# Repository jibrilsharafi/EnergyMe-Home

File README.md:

#  EnergyMe-Home

<div align="center">

<h3>🛒 Want it ready to use? Pre-assembled and calibrated units. Just install and monitor!</h3>

Available on our <a href="https://www.energyme.net/shop">website</a> and on <a href="https://www.tindie.com/stores/energyme/">Tindie</a>

</div>

*EnergyMe-Home* is an open-source energy monitoring system for home use, capable of monitoring up to 16 circuits. It integrates with any platform through REST API, MQTT, Modbus TCP, and InfluxDB.

Built for makers and DIY enthusiasts who want to track their home's energy consumption. The hardware uses ESP32-S3 and ADE7953 energy measurement IC, while the firmware is written in C++ with PlatformIO and Arduino framework. You can build and customize it yourself - all hardware designs and software are open-source. Prefer it ready to go? Grab a [pre-assembled unit](https://www.energyme.net/shop).

> A demo speaks more than 1000 words: try the [demo dashboard](https://demo-energyme-home.energyme.net)!

> **Join the community!** Head over to [GitHub Discussions](https://github.com/jibrilsharafi/EnergyMe-Home/discussions) - ask questions, share your builds and dashboards, suggest features, and exchange integration tips. It's the home for everyone building, installing, or tinkering with EnergyMe-Home

## Supported Electrical Systems

EnergyMe-Home is compatible with various electrical systems worldwide:

| System Type | Voltage | Configuration | Supported |
|-------------|---------|---------------|-----------|
| **Single Phase** | 230V | L + N | ✅ Europe, Asia, Africa, Oceania |
| **Split Phase** | 120V/240V | L1 + L2 + N | ✅ North America residential |
| **Split Phase** | 120V/240V | L1 + L2 (no N) | ✅ Old electrical systems |
| **Three Phase** | 400V/230V | 3L + N | ❕ Europe commercial/industrial (derived voltages) |
| **Three Phase** | 208V/120V | 3L + N | ❕ North America commercial (derived voltages) |

**Current Transformers Supported:**

- 333 mV output CTs (+- 500 mV absolute)
- 3.5 mm jack connectors for easy plug-and-play

**Monitoring Capacity:**

- Up to **16 circuits** simultaneously
- 1× main circuit, sampled at high frequency for accurate total energy measurement
- 15× branch circuits, multiplexed for individual monitoring

⚠️ **Important**: Installation requires working with your main electrical panel. Always consult a qualified electrician if you're not experienced with electrical installations. The user is responsible for ensuring compliance with local electrical codes and regulations, and assumes all risks associated with the installation and use of this device.

## Hardware

The hardware (currently at **v6.1**) consists of both the PCB design and the components used to build the energy monitoring system.

The key components include:

- **ESP32-S3**: the brain of the project
- **ADE7953**: single-phase energy measurement IC
- **ZMPT107-1**: voltage transformer providing **full galvanic isolation** between the AC mains and the low-voltage measurement circuitry, with no direct connection between mains and the board's ground
- **Multiplexers**: used to monitor multiple circuits at once
- **3.5 mm jack connectors**: used to easily connect current transformers

PCB schematics and BOMs are available in the `hardware/pcb` directory, while datasheets for key components are in the `hardware/components` directory. Additional hardware specifications and technical details can be found in the [`hardware/README.md`](hardware/README.md), with a condensed one-page summary in the [PCB & Firmware Datasheet](hardware/datasheet.md).

The project is published on *EasyEDA* for easy access to the PCB design files. You can find the project on [EasyEDA OSHWLab](https://oshwlab.com/jabrillo/multiple-channel-energy-meter).

## Software

The firmware is built with C++ using the *PlatformIO* ecosystem and *Arduino 3.x framework*, with a **task-based architecture using FreeRTOS**.

**Key Features:**

- **Energy Monitoring**: ADE7953 driver with energy accumulation and CSV logging
- **Channel Roles**: Load, grid, PV, battery, hybrid inverter and bidirectional channels, with automatic CT reversal detection
- **Web Interface**: Dashboard for monitoring and system configuration
- **Authentication**: HTTP Digest with forced default-password change and brute-force lockout
- **Integration Options**: REST API, MQTT, InfluxDB, and Modbus TCP
- **Crash Recovery**: Automatic recovery, firmware rollback and core dump archive
- **WiFi Setup**: Captive portal for configuration and mDNS support (`energyme.local`)
- **OTA Updates**: Firmware updates with MD5 verification and rollback (cloud updates are signature-verified)
- **Device Health**: Issue registry (CT polarity, over-temperature, ...) and grid blackout detection
- **Waveform Analyzer**: Capture high-resolution voltage & current waveforms per channel from the web UI

For detailed architecture, implementation details, and API documentation, see [`source/README.md`](source/README.md).

## Integration

EnergyMe-Home offers multiple integration options:

- **REST API**: Complete Swagger-documented API for all data and configuration ([swagger.yaml](source/resources/swagger.yaml))
- **MQTT**: Publish energy data to any MQTT broker with optional authentication
- **Modbus TCP**: Industrial protocol for SCADA systems integration
- **InfluxDB**: Support for both v1.x and v2.x with SSL/TLS and buffering
- **Home Assistant**: Dedicated custom integration ([homeassistant-energyme](https://github.com/jibrilsharafi/homeassistant-energyme))

For detailed integration guides and implementation details, see the [source README](source/README.md).

## Home Assistant Integration

EnergyMe-Home integrates with Home Assistant through a dedicated custom integration.

- **Setup**: Requires device IP address (automatic discovery via mDNS coming soon)
- **Data**: All energy measurements and system information as Home Assistant entities
- **Access**: Monitor all circuits and aggregate data within Home Assistant

Get started at [homeassistant-energyme](https://github.com/jibrilsharafi/homeassistant-energyme).

## Getting Started

1. **Order the PCB**: Download the design files from the [Schematics folder](hardware/pcb/) and order from your preferred PCB manufacturer
2. **Populate the board**: Solder all components using the BOMs in `hardware/pcb/main_board/`, `hardware/pcb/top_board_1/`, and `hardware/pcb/top_board_2/`
3. **Flash the firmware**: Connect a USB-to-UART adapter to the UART pins and flash using PlatformIO
4. **Configure WiFi**: Power on the device and connect to the captive portal to set up WiFi credentials
5. **Start monitoring**: Access the web interface at `http://energyme.local` (default credentials: *admin*/*energyme*, you will be asked to change the password at first login)

For detailed build instructions and troubleshooting, see the [manual](manual/README.md).

## Privacy & Telemetry

Optional anonymous usage statistics sent once per boot: hashed device ID, firmware version, country/city (from public IP). Helps count active installations. No personal data or usage patterns collected. Disable in `platformio.ini`: set `ENABLE_OPEN_SOURCE_TELEMETRY=0`.

## Releases

Firmware binaries and per-version release notes are published on [GitHub Releases](https://github.com/jibrilsharafi/EnergyMe-Home/releases). See [CHANGELOG.md](CHANGELOG.md) for an index of versions and links to the corresponding pull requests.

## Contributing

Contributions are welcome! Please read the [contributing guidelines](CONTRIBUTING.md) for more information.

## License

This project contains both software and hardware components:

- **Software**: Licensed under the [GNU General Public License v3.0](LICENSE) (GPL-3.0)
- **Hardware**: Licensed under the [CERN Open Hardware Licence Version 2 - Strongly Reciprocal](LICENSE-HARDWARE) (CERN-OHL-S-2.0)

See the respective license files for full details.

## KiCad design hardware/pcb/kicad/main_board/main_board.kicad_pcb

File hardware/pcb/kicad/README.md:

# KiCad projects (derived from the EasyEDA backups)

One KiCad 10 project per board, generated from `../backup_easy_eda/*.json` by
the `kicad3d-easyeda-import` tool of the `energyme-3d` repo and used by it to
build the 3D models (GLB for the web, STEP for mechanical CAD, the assembled
device model).

| Board | Source | Contents |
|---|---|---|
| `main_board/` | `pcb_main_board.json` | 87 footprints, 50 x 87 mm, 8 slots + the DIN clip notch |
| `top_board_1/` | `pcb_top_board_1.json` | CH2/CH3 on header H1, stacks on the main board's H2 |
| `top_board_2/` | `pcb_top_board_2.json` | CH10..CH15 on header H4, stacks on the main board's H3 |

`EASYEDA_MODELS/` next to each board holds the LCSC 3D models (`.wrl` for
KiCad's renderer, `.step` twin for the STEP export) fetched with
easyeda2kicad. They are committed because the EasyEDA API rate-limits and
drops parts over time; U2/U4 (ZX-QC66 buttons) have no model at all.

Regenerate after an EasyEDA change (from the `energyme-3d` checkout):

```bash
uv run kicad3d-easyeda-import --json <this repo>/hardware/pcb/backup_easy_eda/pcb_main_board.json --out <this repo>/hardware/pcb/kicad/main_board/main_board.kicad_pcb
uv run kicad3d-attach-models --board <this repo>/hardware/pcb/kicad/main_board/main_board.kicad_pcb --bom <this repo>/hardware/pcb/main_board/BOM_*.csv
```

The import rewrites Edge.Cuts as outer contour minus the union of the EasyEDA
cutouts; without that KiCad's exporters drop every slot.

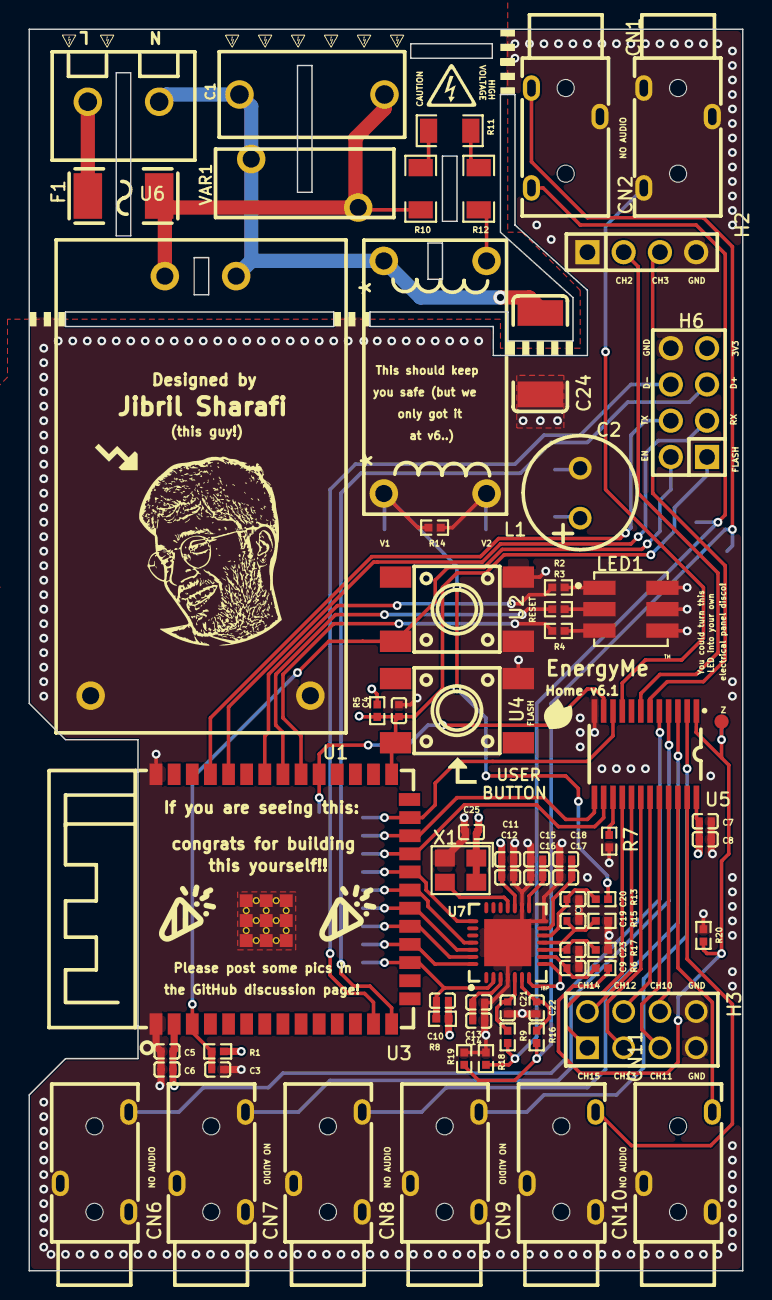
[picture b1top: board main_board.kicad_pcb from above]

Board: 4 copper layers, 50.0 x 87.0 mm, 87 parts (0 on the bottom side), 60 nets.

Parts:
C1: 100nF; CAP-TH_L13.0-W6.0-P10.00-D1.0
C2: 3300uF; CAP-TH_BD8.0-P3.50-D0.6-FD
C3, C6, C8, C12, C14, C16, C18: 10uF; C0402
C4, C5, C7, C10, C11, C13, C15, C17, C25: 100nF; C0402
C9, C19, C20, C21, C22, C23: 33nF; C0402
C24: 1nF; C2211
CN1, CN2, CN6, CN7, CN8, CN9, CN10, CN11: PJ-3200; AUDIO-TH_PJ-3200
F1: JFC2410-0500TS; F2410
H2: PM254V-11-04-H85; HDR-TH_4P-P2.54-V-F
H3: PM254V-12-08-H85_C2834799; HDR-TH_8P-P2.54-V-F-R2-C4-S2.54
H6: PZ254V-12-8P; HDR-TH_8P-P2.54-V-M-R2-C4-S2.54
L1: ZMPT107-1; XFMR-TH_ZMPT107-1
LED1: TC5050RGBF08-3CJH-AF53A; LED-SMD_6P-L5.0-W5.0-TL_TC5050RGBF08
Pad_gge151921: Pad_gge151921
Pad_gge152239: Pad_gge152239
Pad_gge152290: Pad_gge152290
Pad_gge152317: Pad_gge152317
Pad_gge152344: Pad_gge152344
Pad_gge152371: Pad_gge152371
Pad_gge152398: Pad_gge152398
Pad_gge152517: Pad_gge152517
Pad_gge153190: Pad_gge153190
Pad_gge153217: Pad_gge153217
Pad_gge153244: Pad_gge153244
Pad_gge153271: Pad_gge153271
Pad_gge157644: Pad_gge157644
Pad_gge157767: Pad_gge157767
Pad_gge157888: Pad_gge157888
Pad_gge165863: Pad_gge165863
Pad_gge165890: Pad_gge165890
Pad_gge166044: Pad_gge166044
Pad_gge166065: Pad_gge166065
R1, R5, R7, R8: 10kΩ; R0402
R2, R3, R4, R6, R9, R13, R15, R16, R17: 1kΩ; R0402
R10, R11, R12: 51kΩ; R1206
R14: 180Ω; R0402
R18, R19, R20: 1MΩ; R0402
U1: HLK-PM03; PWRM-TH_HLK-PM03
U2, U4: ZX-QC66-7.5TP; KEY-SMD_4P-L6.0-W6.0-P4.50-LS8.6
U3: ESP32-S3-WROOM-1(N16R2); WIRELM-SMD_ESP32-S3-WROOM-1
U5: 74HC4067PW,118; TSSOP-24_L7.8-W4.4-P0.65-LS6.4-BL
U6: DB301V-5.0-2P; CONN-TH_2P-P5.00_L7.6-W10.0
U7: ADE7953ACPZ-RL; LFCSP-28_L5.0-W5.0-P0.50-BL-EP
VAR1: 561KD10; RES-TH_L12.5-W4.8-P7.50-D1.2-S3.40
X1: 3.579545MHz; OSC-SMD_4P-L3.2-W2.5-BL_FT3HNBPK16.0-T1

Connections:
3V3: C2.1, C5.2, C6.2, C7.2, C8.2, C10.2, C11.2, C12.2, C25.1, H6.7, Pad_gge166044.1, R1.2, R5.2, R8.2, U1.4, U3.2, U5.24, U7.7, U7.8, U7.17, X1.1, X1.4
CLKIN: U7.18, X1.3
CS: Pad_gge152371.6, Pad_gge152398.7, U3.18, U7.28
CT0_N: CN1.3, Pad_gge165890.1, R16.2, R19.2
CT0_P: CN1.4, Pad_gge165863.1, R9.1, R18.2
CT1: CN2.4, U5.9
CT3: H2.2, U5.7
CT4: H2.3, U5.6
CT5: CN6.4, U5.5
CT6: CN7.4, U5.4
CT7: CN8.4, U5.3
CT8: CN9.4, U5.2
CT9: CN10.4, U5.23
CT10: CN11.4, U5.22
CT11: H3.6, U5.21
CT12: H3.5, U5.20
CT13: H3.4, U5.19
CT14: H3.3, U5.18
CT15: H3.2, U5.17
CT16: H3.1, U5.16
EN: C3.2, H6.2, R1.1, U2.3, U3.3
FLASH: C4.2, H6.1, R5.1, U3.27, U4.3
GND: C2.2, C3.1, C4.1, C5.1, C6.1, C7.1, C8.1, C9.1, C11.1, C12.1, C13.1, C14.1, C15.1, C16.1, C17.1, C18.1, C19.1, C20.1, C21.1, C22.1, C23.1, C24.2, C25.2, CN1.2, CN2.2, CN2.3, CN6.2, CN6.3, CN7.2, CN7.3, CN8.2, CN8.3, CN9.2, CN9.3, CN10.2, CN10.3, CN11.2, CN11.3, H2.4, H3.7, H3.8, H6.8, L1.2, LED1.4, LED1.5, LED1.6, Pad_gge157767.1, Pad_gge166065.1, R7.2, R14.1, R15.2, R17.1, R18.1, R19.1, R20.1, U1.3, U2.2, U3.1, U3.40, U3.41, U4.2, U5.12, U7.4, U7.14, U7.16, U7.29, X1.2
IAN: C22.2, R16.1, U7.6
IAP: C21.2, R9.2, U7.5
IBN: C23.2, R17.2, U7.10
IBP: C9.2, R6.1, U7.9
L: F1.1, U6.2
L1_4: L1.4, R12.2
LED1_1: LED1.1, R2.2
LED1_2: LED1.2, R3.2
LED1_3: LED1.3, R4.2
LED_B: R4.1, U3.32
LED_G: R2.1, U3.34
LED_R: R3.1, U3.33
L_FUSE: C1.1, F1.2, R10.1, U1.2, VAR1.2
MISO: Pad_gge152317.4, U3.20, U7.26
MOSI: Pad_gge152344.5, U3.19, U7.27
N: C1.2, C24.1, L1.3, U1.1, U6.1, VAR1.1
QRI#: Pad_gge152239.2, U3.22, U7.22
R10_2: R10.2, R11.1
R11_2: R11.2, R12.1
R13_1: L1.1, Pad_gge157644.1, R13.1, R14.2
REF_IN_OUT: C17.2, C18.2, U7.13
RST_ADE: C10.1, Pad_gge152517.9, R8.1, U3.17, U7.2
RX: H6.3, U3.36
S0: Pad_gge153244.12, U3.25, U5.10
S1: Pad_gge153271.13, U3.31, U5.11
S2: Pad_gge153190.10, U3.23, U5.14
S3: Pad_gge153217.11, U3.24, U5.13
SCLK: Pad_gge152290.3, U3.21, U7.25
TX: H6.4, U3.37
U5_1: Pad_gge151921.1, Pad_gge157888.1, R6.2, R20.2, U5.1
U5_15: R7.1, U5.15
USB_DN: H6.6, U3.13
USB_DP: H6.5, U3.14
VINTA: C15.2, C16.2, U7.15
VINTD: C13.2, C14.2, U7.3
VN: C20.2, R15.1, U7.11
VP: C19.2, R13.2, U7.12

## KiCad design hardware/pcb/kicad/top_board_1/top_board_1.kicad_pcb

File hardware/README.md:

# EnergyMe-Home Hardware Documentation

This document provides detailed hardware specifications and technical information for the EnergyMe-Home PCB design. For general project information, software features, and integrations, see the [main README](../README.md). For a condensed one-page specification of the PCB and firmware, see the [PCB & Firmware Datasheet](datasheet.md).

Now, take a look at these beautiful renderings of the PCB design before diving into the technical details:

## Hardware Specifications

**Board Information:**

- **Hardware Revision:** v6.1
- **PCB Layers:** 4 layers
- **Board Dimensions:** 87 mm x 50 mm. Height with components around 15 mm
- **Power Consumption:** ~200 mA @ 3.3V typical (~ 1W AC consumption)

**Key Components:**

- **Main Microcontroller:** ESP32-S3-WROOM-1-N16R2 (dual-core, WiFi 2.4 GHz, 16MB Flash, 2MB PSRAM)
- **Energy Measurement IC:** Analog Devices ADE7953ACPZ-RL (single-phase, dual-channel)
- **ADE7953 Oscillator:** 3.58 MHz active SMD oscillator (RO03579043), more compact than a crystal+load-cap pair and requiring no additional passive components
- **Analog Multiplexer:** 74HC4067PW,118 (16-channel, TSSOP-24)
- **CT Inputs:** 16× PJ-3200 3.5mm stereo jacks (1 direct + 15 multiplexed). The plastic housing prevents shorts when stacking the expansion boards on top of the main board.
- **Voltage Transformer:** ZMPT107-1 for AC mains reference with full galvanic isolation
- **Power Supply:** HLK-PM03 AC/DC module (100-240 VAC to 3.3 VDC, 1A max)

**ESP32-S3 Module Compatibility Notes:**

The design uses ESP32-S3-WROOM-1-N16R2 with quad PSRAM (2MB). Other ESP32-S3 variants may work with `platformio.ini` and partition adjustments, but note:

- **N16R8 (8MB Octal PSRAM)**: Octal PSRAM uses GPIOs 35, 36, 37 and such pins are not used for this exact reason, thus making it compatible with the current design. However, the firmware is not tested on this variant yet.
- **N16R0, N8R0, N4R0 (No PSRAM)**: May work with firmware adjustments but not tested - PSRAM used for queues and JSON documents throughout the code
- **N16R2, N8R2, N4R2 (2MB Quad PSRAM)**: Should work with partition table adjustments. Compiled firmware ~2MB (see [issue #21](https://github.com/jibrilsharafi/EnergyMe-Home/issues/21))

## Circuit Design Overview

### 1. Power Supply Unit

The *HLK-PM03* AC/DC module provides isolated 3.3V DC from universal AC input (100-240 VAC, 50-60 Hz). It is suitable for any region and more than enough for the low power requirements of the board.

The power supply section includes:

- **Protection components**
  - Fuse (500 mA slow-blow) on the AC line for overcurrent protection
  - Varistor (MOV) for surge protection
  - PCB slots for physical isolation and safety compliance
- **EMI suppression components**
  - Class X2 100nF film capacitor across the AC line for mains EMI suppression
  - Large 3300µF bulk capacitor on the DC rail for hold-up time after grid loss, allowing the ADE7953 to detect missing voltage reference and for the firmware to dispatch a last-gasp MQTT message before power fails.
  - SMD 1 nF capacitor on the secondary side of the voltage transformer to stitch the floating output to analog ground, suppressing common-mode noise introduced by the isolation barrier

### 2. Microcontroller (ESP32-S3)

*ESP32-S3-WROOM-1-N16R2*: the central processing unit managing all digital logic, SPI communication with ADE7953, multiplexer control, LED control, and wireless connectivity. *The beast*.

### 3. Energy Measurement (ADE7953)

High-precision 24-bit energy metering IC (*ADE7953ACPZ-RL*) with dual current channels (A and B), clocked by a 3.58 MHz active SMD oscillator, and low-pass filters on all analog inputs (1 kΩ / 33 nF). Key features:

- **Voltage Input:** AC mains reference via ZMPT107-1 voltage transformer (full galvanic isolation)
- **Channel A:** Direct CT input for main circuit monitoring (usually the grid in single phase systems)
- **Channel B:** Multiplexed input from 15 branch circuits
- **Communication:** SPI interface to ESP32-S3 at 2 MHz, with an interrupt line for data-ready notifications (IRQ)

### 4. Analog Multiplexing

*74HC4067PW,118* multiplexer routes one of 15 CT signals to ADE7953 Channel B. ESP32-S3 controls select lines (S0-S3) for sequential measurement. Supports +- 0.5 V relative to ground, which is sufficient for voltage-output CTs (max 333 mV).

### 5. CT Interface & Other Inputs

All 16 CT inputs use PJ-3200 3.5mm stereo jacks with direct connection through low-pass filters (1 kΩ / 33 nF). **Maximum CT output: 333 mV**. No burden resistors are present on the board. 1 MΩ resistors are placed on the CT inputs to guarantee 0 V readings on the ADE7953 when no CT is connected, preventing floating inputs from causing spurious measurements. The PJ-3200 plastic housing is important when stacking the top expansion boards on top of the main board, as it prevents accidental shorts between the jack body and the board above.

The line voltage is fed to the ZMPT107-1 voltage transformer via a 2.54mm 2-pin screw terminal block, rated for 300V/3A.

The programming header is a standard 2x4 2.54mm pin header, comprising of 3V3, GND, EN, IO0, TX, RX, D+, D- pins.

Two more headers are available for expanding the CT inputs up to 16 total channels (the bare board has 8 channels).

## PCB Layout & Design

The main board features a **4-layer PCB** design. The components, present only on the top side, are both SMD and through-hole, with the majority being SMD for compactness.

**Layer Stack-up:**

- **Layer 1 (Top):** Signal routing, components
- **Layer 2:** Ground plane (continuous pour for low impedance)
- **Layer 3:** Power plane (3.3V distribution)
- **Layer 4 (Bottom):** Signal routing

**Component Placement:**

- **Power section** isolated on top-left side with HLK-PM03 AC/DC module and ZMPT107-1 voltage transformer
- **ESP32-S3** positioned on the left side, leaving a slot under the PCB antenna on the module to improve WiFi performance
- **ADE7953** placed close to the ESP32-S3 to minimize SPI trace lengths
- **Multiplexer** positioned close to the ADE7953 to reduce analog signal path lengths
- **CT jacks** arranged in rows along board edges for easy access
- **RGB LED** near the center for status indication
- **Tactile buttons** for user input located at the center for easy access
- **Programming header** located at the center for easier access
- **Expansion headers** near the CT jacks for additional channels

**Main Board Layout:**

## Design Files & Resources

All design files (PCB layouts, BOMs, Gerber files, Pick-and-Place files) are grouped by board (main_board, top_board_1, top_board_2), while the schematics are provided in a single PDF.

- **EasyEDA Project:** [OSHWLAB | EnergyMe - Home](https://oshwlab.com/jabrillo/multiple-channel-energy-meter)
- **Schematics:** `pcb/schematics.pdf` (PNG pages: `pcb/schematics_page_1.png` to `pcb/schematics_page_5.png`)
- **BOM:** `pcb/main_board/bom_main_board.csv`, `pcb/top_board_1/bom_top_board_1.csv`, `pcb/top_board_2/bom_top_board_2.csv`
- **Gerber Files:** `pcb/main_board/gerber_main_board.zip`, `pcb/top_board_1/gerber_top_board_1.zip`, `pcb/top_board_2/gerber_top_board_2.zip`
- **PCB Layout PDFs:** `pcb/main_board/pcb_main_board_top.pdf`, `pcb/main_board/pcb_main_board_bottom.pdf`, `pcb/top_board_1/pcb_top_board_1_top.pdf`, `pcb/top_board_1/pcb_top_board_1_bottom.pdf`, `pcb/top_board_2/pcb_top_board_2_top.pdf`, `pcb/top_board_2/pcb_top_board_2_bottom.pdf`
- **Pick-and-Place Files:** `pcb/main_board/pick_and_place_main_board.csv`, `pcb/top_board_1/pick_and_place_top_board_1.csv`, `pcb/top_board_2/pick_and_place_top_board_2.csv`
- **EasyEDA Backup:** `pcb/backup_easy_eda/` (schematic and PCB JSON files)
- **Component Datasheets:** Available in `components/` directory

## Hardware Versions and Compatibility

Firmware 2.0.0 selects its hardware profile at runtime from the NVS key `factory_ns::pcb_revision`, matched against the entries in `source/src/hardware_profile.cpp::PCB_PROFILES[]`.

- **v6.1** (current production): 16 channels (1 direct + 15 multiplexed via 74HC4067), ZMPT107-1 voltage transformer.
- **v5 and earlier**: not supported by 2.0.x firmware. Existing v5 devices stay on the 1.x line; critical fixes are cherry-picked to the `legacy/v5` branch.
- **Community / self-built boards** (no factory NVS provisioning): the firmware falls back to the profile selected by the `-DPCB_VERSION_FALLBACK` build flag in `platformio.ini` (or to `PCB_PROFILES[0]` if unset) and starts in **community mode**: cloud services are disabled, all local integrations (REST API, Modbus TCP, custom MQTT, InfluxDB) remain fully functional.

## Safety Notes

⚠️ **ELECTRICAL SAFETY WARNING**

This device interfaces with AC mains voltage. Construction and installation must only be performed by qualified individuals with proper knowledge of electrical safety. Improper handling can result in serious injury or death.

## Hardware Images

**Top view (bare PCB):**

**Bottom view (bare PCB):**

**Top view (assembled):**

**Bottom view (assembled):**

**Front:**

**Back:**

**Left:**

**Right:**

**With CTs connected:**

**CT jack detail:**

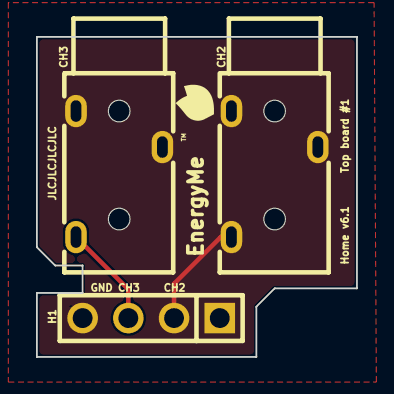
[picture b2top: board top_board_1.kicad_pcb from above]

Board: 2 copper layers, 17.8 x 17.8 mm, 3 parts (0 on the bottom side), 3 nets.

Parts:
CH2, CH3: PJ-3200; AUDIO-TH_PJ-3200
H1: PZ254V-11-04P_C2691448; HDR-TH_4P-P2.54-V-M

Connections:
CT3_T: CH2.4, H1.2
CT4_T: CH3.4, H1.3
GND: CH2.2, CH2.3, CH3.2, CH3.3, H1.4

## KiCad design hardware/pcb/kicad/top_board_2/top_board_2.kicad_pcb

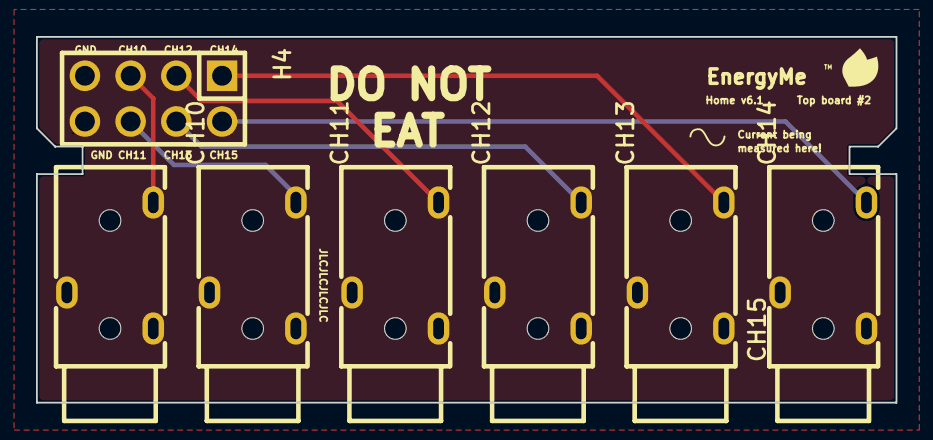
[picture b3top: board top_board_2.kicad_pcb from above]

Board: 2 copper layers, 47.8 x 20.3 mm, 7 parts (0 on the bottom side), 7 nets.

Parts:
CH10, CH11, CH12, CH13, CH14, CH15: PJ-3200; AUDIO-TH_PJ-3200
H4: PZ254V-12-8P; HDR-TH_8P-P2.54-V-M-R2-C4-S2.54

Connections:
CT11_T: CH10.4, H4.5
CT12_T: CH11.4, H4.6
CT13_T: CH12.4, H4.3
CT14_T: CH13.4, H4.4
CT15_T: CH14.4, H4.1
CT16_T: CH15.4, H4.2
GND: CH10.2, CH10.3, CH11.2, CH11.3, CH12.2, CH12.3, CH13.2, CH13.3, CH14.2, CH14.3, CH15.2, CH15.3, H4.7, H4.8
